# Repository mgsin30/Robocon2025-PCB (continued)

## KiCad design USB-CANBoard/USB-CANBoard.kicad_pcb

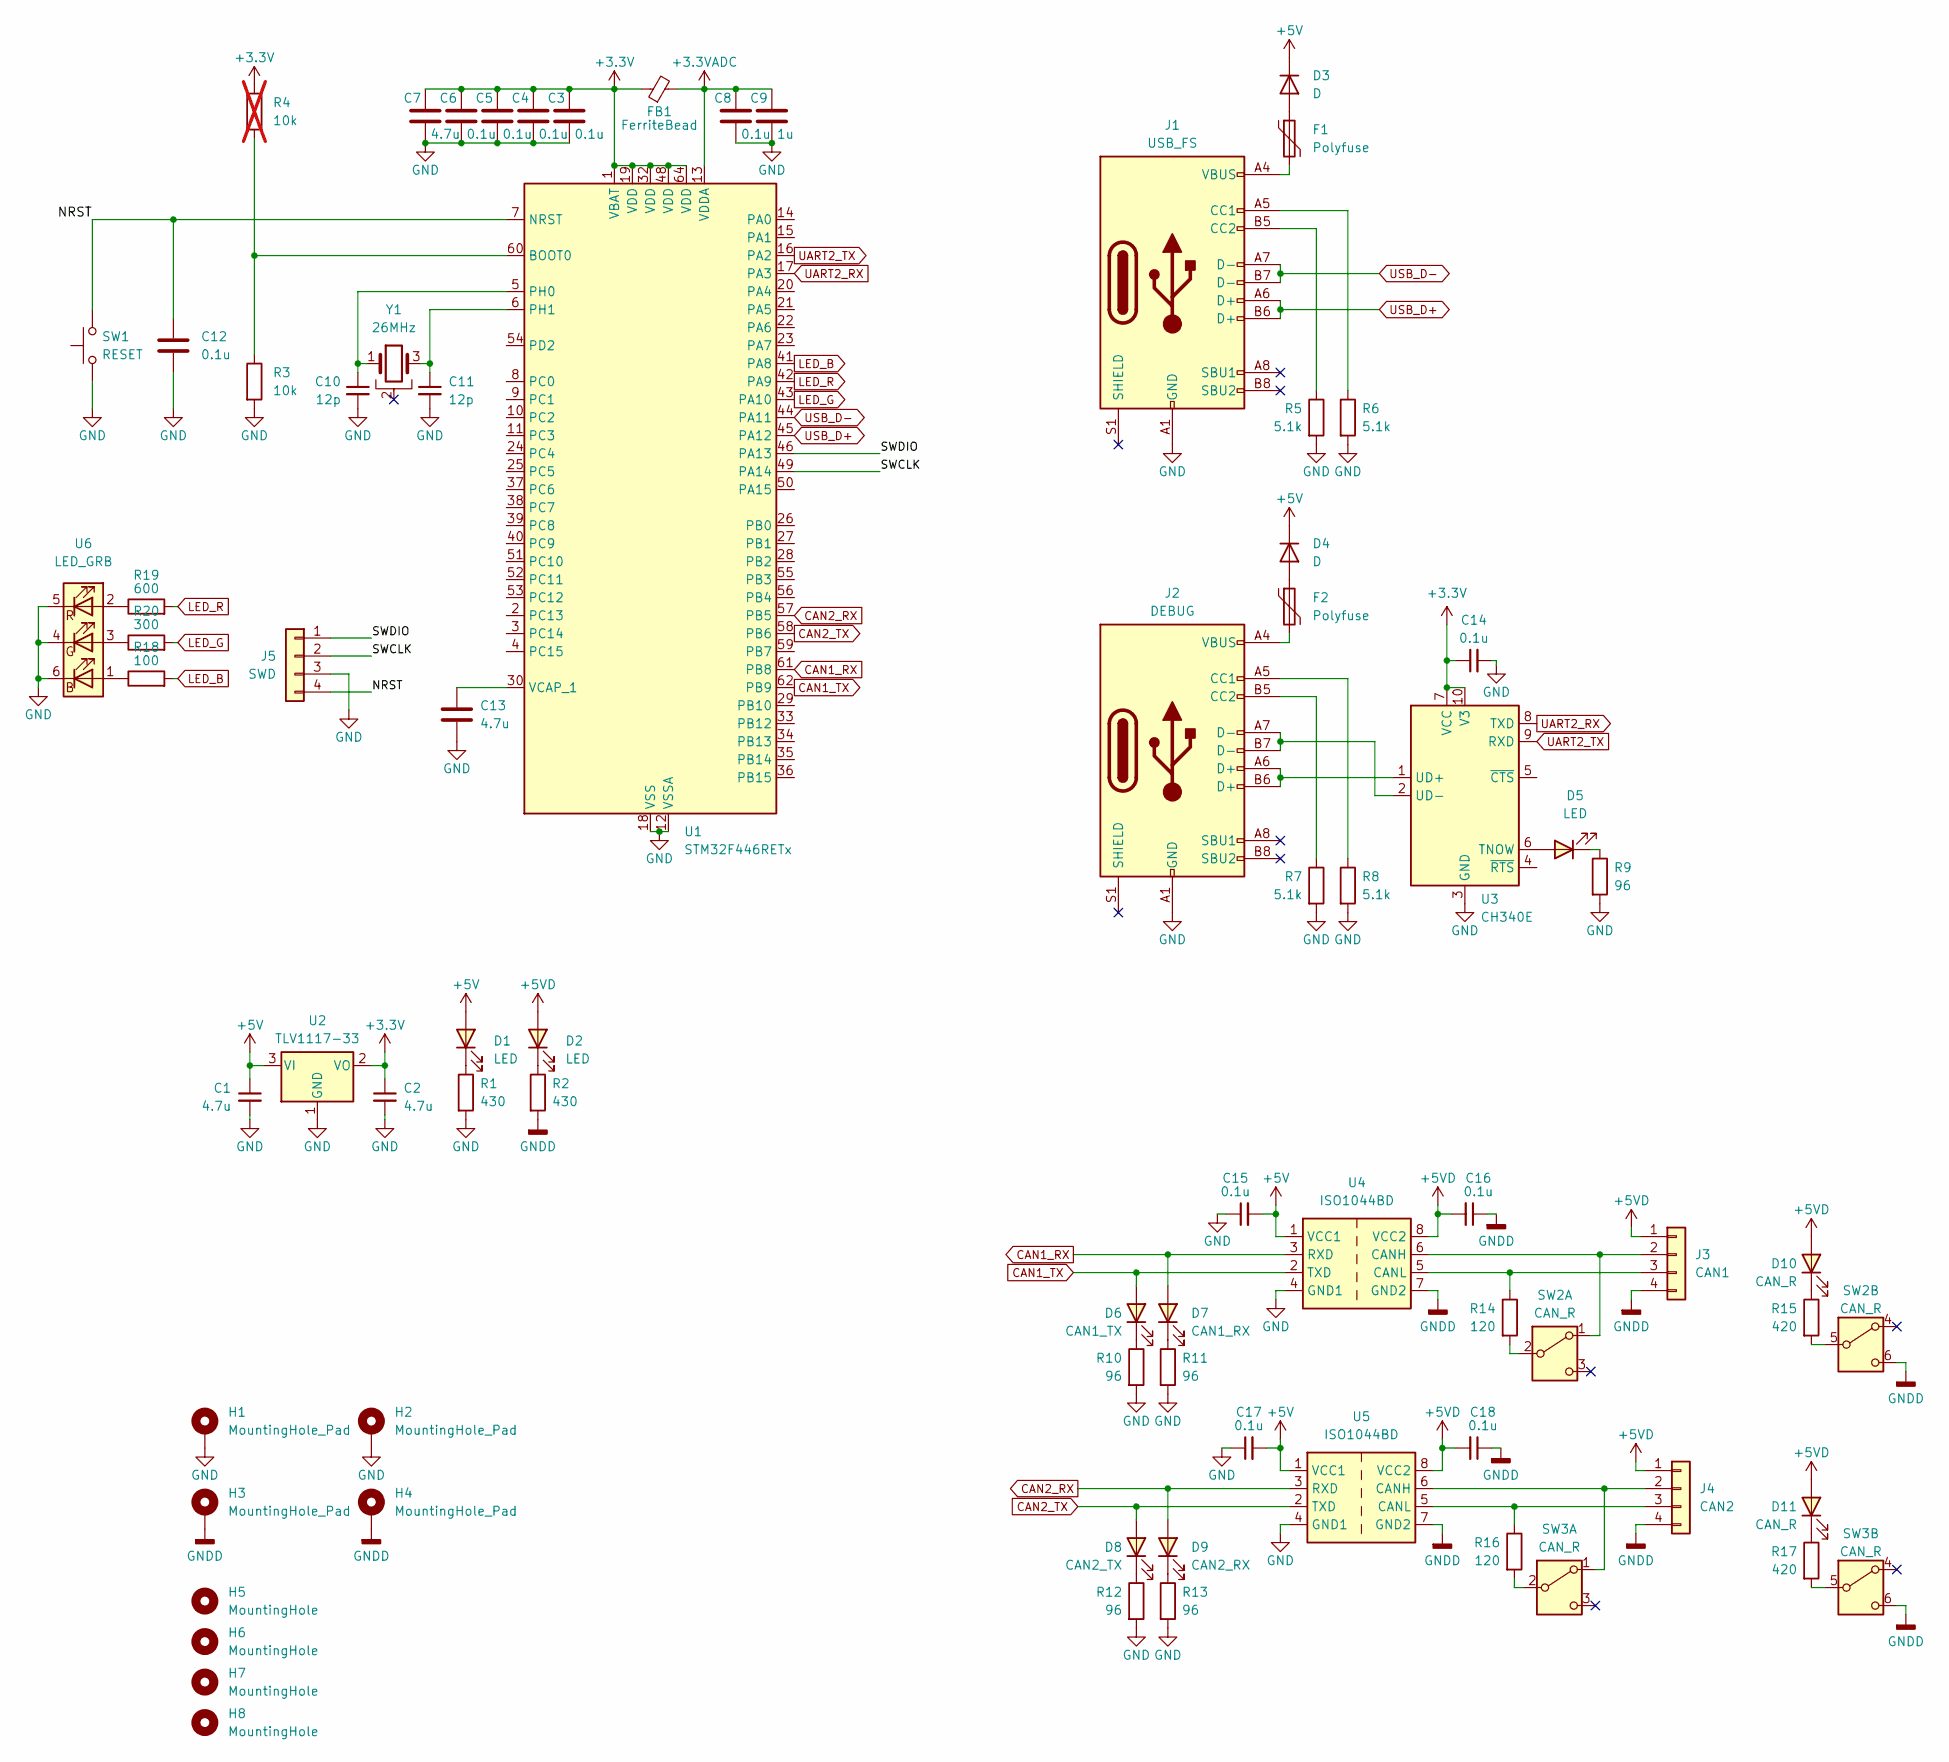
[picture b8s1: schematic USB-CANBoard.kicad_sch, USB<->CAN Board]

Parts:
C1, C2, C7, C13: 4.7u; C_0603_1608Metric
C3, C4, C5, C6, C8, C12, C14, C15, C16, C17, C18: 0.1u; C_0603_1608Metric
C9: 1u; C_0603_1608Metric
C10, C11: 12p; C_0603_1608Metric
D1, D2, D5: LED; LED_0603_1608Metric
D3, D4: D; Nexperia_CFP3_SOD-123W
D6: CAN1_TX; LED_0603_1608Metric
D7: CAN1_RX; LED_0603_1608Metric
D8: CAN2_TX; LED_0603_1608Metric
D9: CAN2_RX; LED_0603_1608Metric
D10, D11: CAN_R; LED_0603_1608Metric
F1, F2: Polyfuse; MF-FSMF
FB1: FerriteBead; L_0603_1608Metric
H1, H2, H3, H4: MountingHole_Pad; MountingHole_3.2mm_M3_Pad
H5: MountingHole; Title
H6: MountingHole; Aho_old_M
H7: MountingHole; Aho_new_M
H8: MountingHole; Info_M
J1: USB_FS; USB_C_Receptacle_GCT_USB4105-xx-A_16P_TopMnt_Horizontal
J2: DEBUG; USB_C_Receptacle_GCT_USB4105-xx-A_16P_TopMnt_Horizontal
J3: CAN1; PAコネクタ(4ピンサイド型)
J4: CAN2; PAコネクタ(4ピンサイド型)
J5: SWD; JST_SH_SM04B-SRSS-TB_1x04-1MP_P1.00mm_Horizontal
R1, R2: 430; R_0603_1608Metric
R3: 10k; R_0603_1608Metric
R4: 10k; R_0603_1608Metric; not fitted
R5, R6, R7, R8: 5.1k; R_0603_1608Metric
R9, R10, R11, R12, R13: 96; R_0603_1608Metric
R14, R16: 120; R_0603_1608Metric
R15, R17: 420; R_0603_1608Metric
R18: 100; R_0603_1608Metric
R19: 600; R_0603_1608Metric
R20: 300; R_0603_1608Metric
SW1: RESET; TVAF06-A020B-R
SW2, SW3: CAN_R; SLW
U1: STM32F446RETx; LQFP-64_10x10mm_P0.5mm
U2: TLV1117-33; SOT-223-3_TabPin2
U3: CH340E; MSOP-10_3x3mm_P0.5mm
U4, U5: ISO1044BD; SOIC-8_3.9x4.9mm_P1.27mm
U6: LED_GRB; LED_ROHM_SMLVN6
Y1: 26MHz; XRCGB

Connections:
+3.3V: C2.1, C3.1, C4.1, C5.1, C6.1, C7.1, C14.1, FB1.1, R4.1, U1.1 (VBAT), U1.19 (VDD), U1.32 (VDD), U1.48 (VDD), U1.64 (VDD), U2.2 (VO), U3.7 (VCC), U3.10 (V3)
+3.3VADC: C8.1, C9.1, FB1.2, U1.13 (VDDA)
+5V: C1.1, C15.2, C17.2, D1.2 (A), D3.1 (K), D4.1 (K), U2.3 (VI), U4.1 (VCC1), U5.1 (VCC1)
+5VD: C16.2, C18.2, D2.2 (A), D10.2 (A), D11.2 (A), J3.1, J4.1, U4.8 (VCC2), U5.8 (VCC2)
/NRST: C12.1, J5.4, SW1.2, U1.7 (NRST)
/SWCLK: J5.2, U1.49 (PA14)
/SWDIO: J5.1, U1.46 (PA13)
CAN1_RX: D7.2 (A), U1.61 (PB8), U4.3 (RXD)
CAN1_TX: D6.2 (A), U1.62 (PB9), U4.2 (TXD)
CAN2_RX: D9.2 (A), U1.57 (PB5), U5.3 (RXD)
CAN2_TX: D8.2 (A), U1.58 (PB6), U5.2 (TXD)
GND: C1.2, C2.2, C3.2, C4.2, C5.2, C6.2, C7.2, C8.2, C9.2, C10.2, C11.2, C12.2, C13.2, C14.2, C15.1, C17.1, H1.1, H2.1, J1.A1 (GND), J1.A12 (GND), J1.B1 (GND), J1.B12 (GND), J2.A1 (GND), J2.A12 (GND), J2.B1 (GND), J2.B12 (GND), J5.3, R1.2, R3.2, R5.2, R6.2, R7.2, R8.2, R9.2, R10.2, R11.2, R12.2, R13.2, SW1.1, U1.12 (VSSA), U1.18 (VSS), U1.31 (VSS), U1.47 (VSS), U1.63 (VSS), U2.1 (GND), U3.3 (GND), U4.4 (GND1), U5.4 (GND1), U6.4, U6.5, U6.6
GNDD: C16.1, C18.1, H3.1, H4.1, J3.4, J4.4, R2.2, SW2.6 (C), SW3.6 (C), U4.7 (GND2), U5.7 (GND2)
LED_B: R18.2, U1.41 (PA8)
LED_G: R20.2, U1.43 (PA10)
LED_R: R19.2, U1.42 (PA9)
unnamed: D1.1 (K), R1.1
unnamed: D2.1 (K), R2.1
unnamed: D3.2 (A), F1.1
unnamed: D4.2 (A), F2.1
unnamed: D5.2 (A), U3.6 (TNOW)
unnamed: D5.1 (K), R9.1
unnamed: D6.1 (K), R10.1
unnamed: D7.1 (K), R11.1
unnamed: D8.1 (K), R12.1
unnamed: D9.1 (K), R13.1
unnamed: D10.1 (K), R15.1
unnamed: D11.1 (K), R17.1
unnamed: F1.2, J1.A4 (VBUS), J1.A9 (VBUS), J1.B4 (VBUS), J1.B9 (VBUS)
unnamed: F2.2, J2.A4 (VBUS), J2.A9 (VBUS), J2.B4 (VBUS), J2.B9 (VBUS)
unnamed: J1.A5 (CC1), R6.1
unnamed: J1.B5 (CC2), R5.1
unnamed: J2.A5 (CC1), R8.1
unnamed: J2.B5 (CC2), R7.1
unnamed: J3.2, SW2.1 (A), U4.6 (CANH)
unnamed: J3.3, R14.1, U4.5 (CANL)
unnamed: J4.2, SW3.1 (A), U5.6 (CANH)
unnamed: J4.3, R16.1, U5.5 (CANL)
unnamed: R18.1, U6.1
unnamed: R19.1, U6.2
unnamed: R20.1, U6.3
unnamed: R14.2, SW2.2 (B)
unnamed: R15.2, SW2.5 (B)
unnamed: R16.2, SW3.2 (B)
unnamed: R17.2, SW3.5 (B)
unnamed: R3.1, R4.2, U1.60 (BOOT0)
unnamed: C10.1, U1.5 (PH0), Y1.1
unnamed: C11.1, U1.6 (PH1), Y1.3
unnamed: C13.1, U1.30 (VCAP_1)
unnamed: J2.A6 (D+), J2.B6 (D+), U3.1 (UD+)
unnamed: J2.A7 (D-), J2.B7 (D-), U3.2 (UD-)
UART2_RX: U1.17 (PA3), U3.8 (TXD)
UART2_TX: U1.16 (PA2), U3.9 (RXD)
USB_D+: J1.A6 (D+), J1.B6 (D+), U1.45 (PA12)
USB_D-: J1.A7 (D-), J1.B7 (D-), U1.44 (PA11)

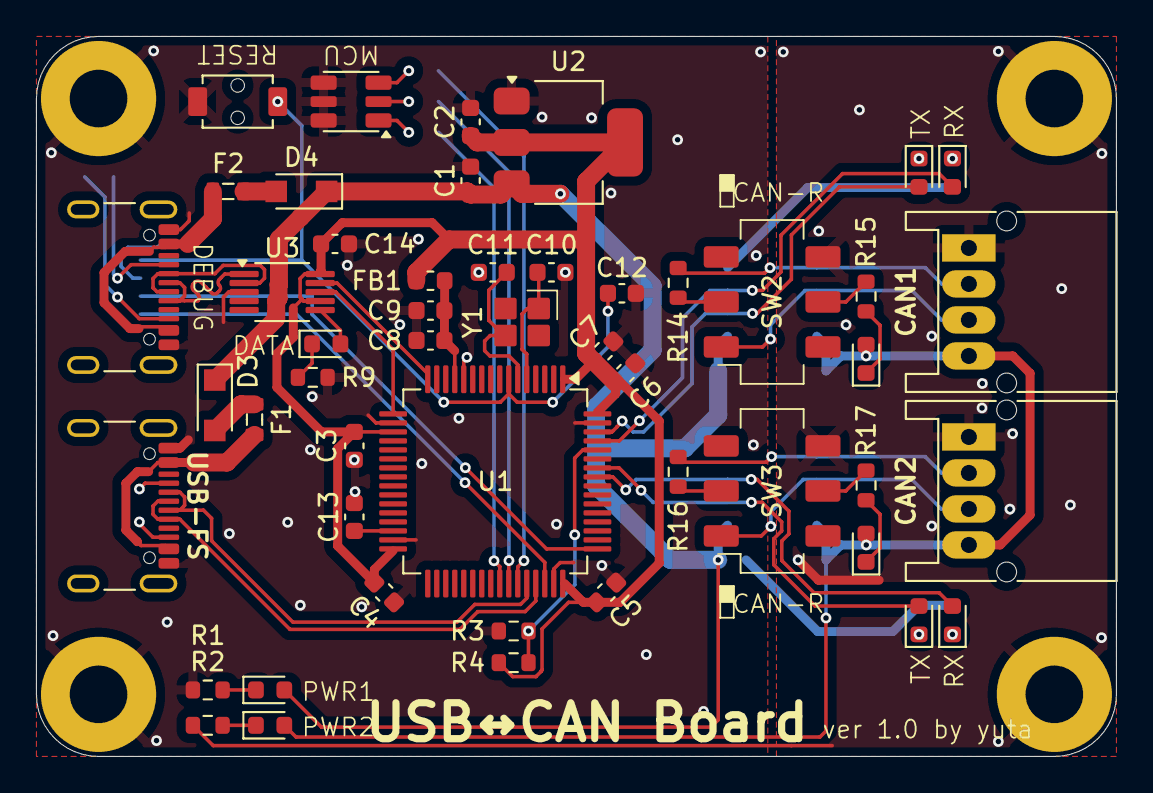
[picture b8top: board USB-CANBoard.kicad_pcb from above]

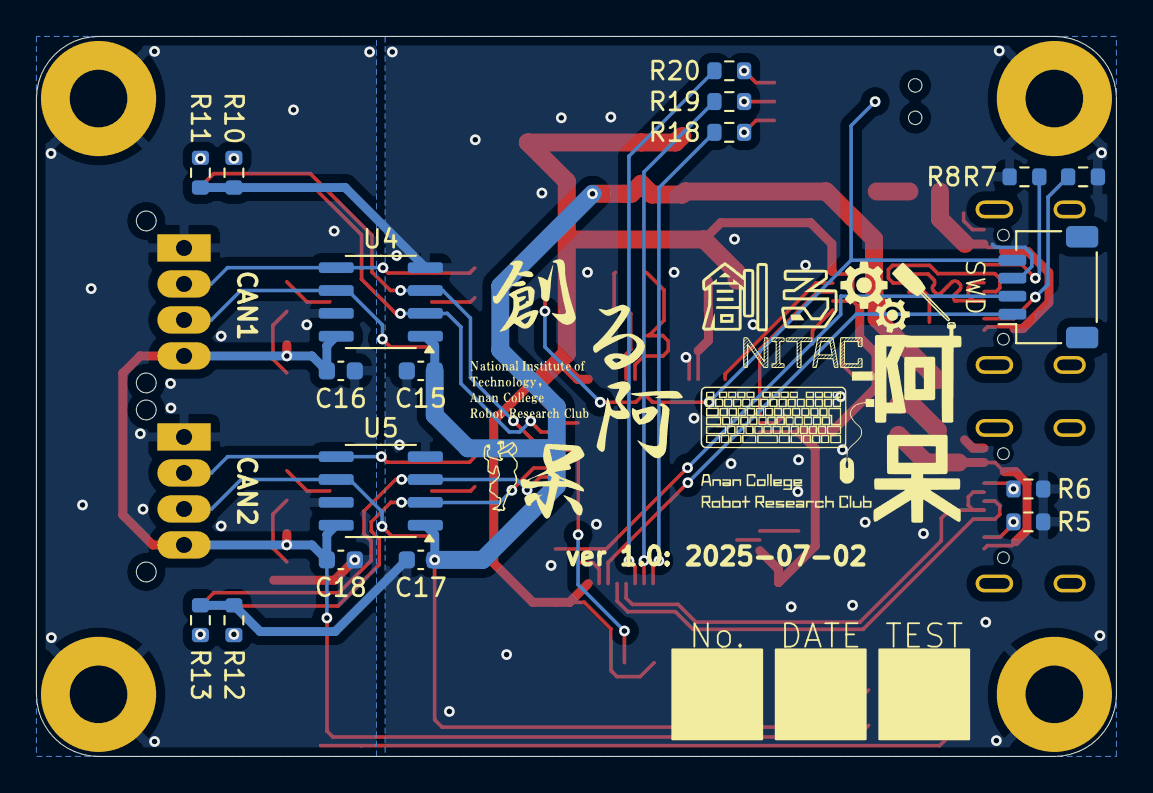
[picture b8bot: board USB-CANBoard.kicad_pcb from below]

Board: 2 copper layers, 60.0 x 40.0 mm, 75 parts (21 on the bottom side), 55 nets.

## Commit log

2025-03-19 GPIO Board ver1.0
2025-03-19 バックアップファイルを追跡対象から除外
2025-04-01 XT30 Hub ver1.0
2025-04-07 XT60 Hub ver1.0
2025-04-07 [XT30Hub] : 裏面の枠線の太さを修正
2025-04-07 [XT30Hub] : 回路図をPDF化
2025-04-07 [XT60Hub] : ガーバーファイルを追加
2025-04-07 [GPIOBoard] : 回路図の一時ファイルを削除
2025-04-12 GPIO Board ver1.1
2025-04-12 PWM Board ver1.0
2025-04-12 RoboMaster Board ver1.0
2025-04-12 Solenoid Driver ver1.0
2025-04-12 [XT30Hub] : 発注前に最終調整
2025-04-12 [XT30Hub] : 基板の画像を追加
2025-04-12 [XT60Hub] : 発注前に最終調整
2025-04-12 [XT60Hub] : 基板の画像を追加
2025-04-13 [GPIOBoard] : 基板の表面と裏面の画像を追加
2025-04-13 [GPIOBoard] : README に説明や画像などを追加
2025-04-13 [GPIOBoard] : 不要な画像を削除
2025-04-13 [PWMBoard] : 基板の表面と裏面の画像を追加
2025-04-13 [GPIOBoard] : 基板の画像をレイトレーシング画像に変更
2025-04-13 [PWMBoard] : 基板の画像をレイトレーシング画像に変更
2025-04-13 [PWMBoard] : 不要な画像を削除
2025-04-13 [PWMBoard] : README を追加
2025-04-13 [RoboMasterBoard] : 基板の画像をレイトレーシング画像に変更
2025-04-13 [RoboMasterBoard] : README を追加
2025-04-13 [SolenoidDriver] : 基板の画像をレイトレーシング画像に変更
2025-04-13 [SolenoidDriver] : README を追加
2025-04-13 [XT30Hub] : 基板の画像をレイトレーシング画像に変更
2025-04-13 [XT30Hub] : README を追加
2025-04-13 [XT60Hub] : 基板の画像をレイトレーシング画像に変更
2025-04-13 [XT60Hub] : README を追加
2025-05-01 Motor Driver ver1.0
2025-06-01 CAN Bus Hub ver1.0
2025-06-01 Converter Board ver1.0
2025-06-01 Power Board ver1.0
2025-06-01 Remote Emergency Stop Board RX ver1.0
2025-06-01 Remote Emergency Stop Board TX ver1.0
2025-06-17 Converter Board ver1.1
2025-06-17 [Converter Board] : 基板上の日付を修正
2025-07-01 GPIO Board ver1.2
2025-07-01 PWM Board ver1.1
2025-07-01 Solenoid Driver ver1.1
2025-07-01 RoboMaster Board ver1.1
2025-07-01 [PWM Board] : 日付の説明を変更
2025-07-05 .kicad_prl を追跡対象から除外
2025-07-12 USB-CAN Board ver1.0
2025-07-12 Motor Driver ver2.0
2025-07-12 コンデンサの容量を修正
2025-07-12 ファームウェアのリポジトリへのリンクと各基板の説明を追加
2025-07-13 CAN Bus Hub ver1.1
2025-07-13 Board Fixer ver1.0
2025-07-14 [Board Base] : 名前を変更
2025-07-15 [Board Base] : 不要なモデルを削除
2025-07-15 基板の3Dモデルを別のフォルダに移動
2025-07-15 GPIO Board ver1.3
2025-07-16 各基板の3Dモデルを追加
2025-07-17 CAN Bus Hub の3Dモデルを更新
2025-07-17 Board Base ver2.0
2025-07-17 [Board Base] : 画像を追加
2025-08-19 Motor Driver ver2.1
2025-09-07 Fan Board ver1.0
2025-09-12 Converter Board ver1.2
2025-09-12 XT30 Hub ver1.1
2025-09-12 XT60 Hub ver1.1
2025-09-27 LED Board ver1.0
2026-03-16 説明文を変更
